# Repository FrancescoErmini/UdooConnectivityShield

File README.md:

# UdooConnectivityShield

Gerber file used to create a shield for UDOO quad board to use XBEE and NFC module by Adafruit.
Video description here: http://www.francescoermini.it/?p=2317

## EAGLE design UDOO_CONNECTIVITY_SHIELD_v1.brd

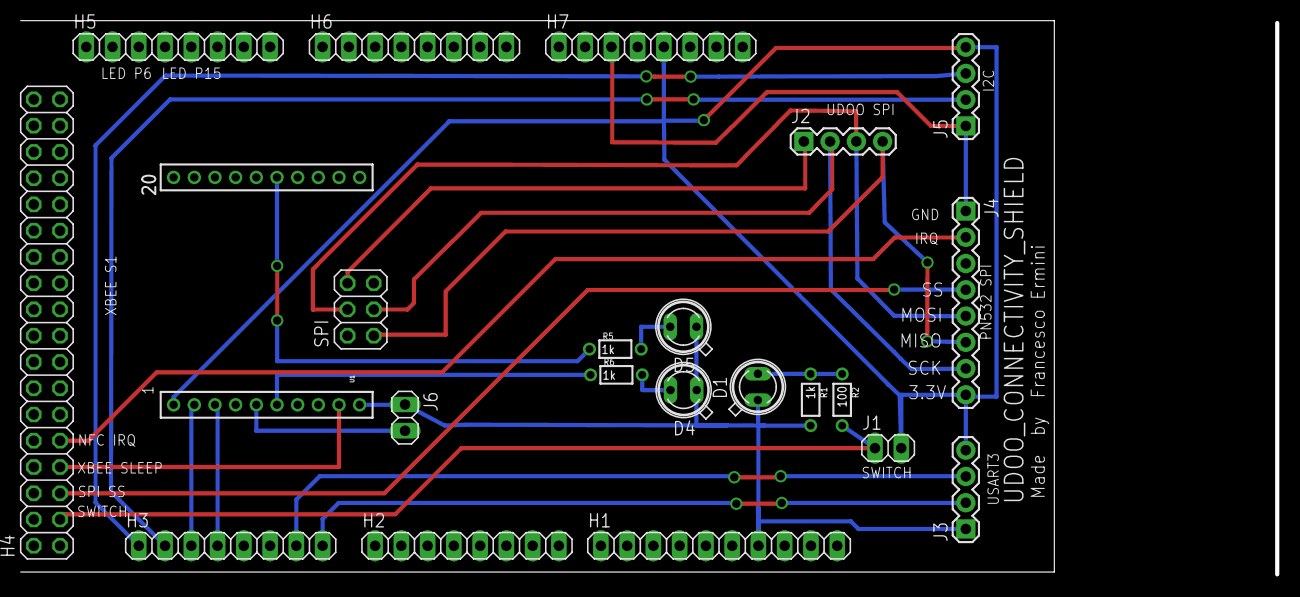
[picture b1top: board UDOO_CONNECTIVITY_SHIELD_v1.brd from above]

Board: 2 copper layers, 121.6 x 53.6 mm, 22 parts (0 on the bottom side), 23 nets.

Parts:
D1, D4, D5: SFH480
H1: 1X10
H2, H3, H5, H6, H7: 1X08
H4: 2X18
J1, J6: 1X02
J2, J3, J5: 1X04
J4: 1X08
R1, R5, R6: 1k; 1/6W-RES
R2: 100; 1/6W-RES
SPI: 2X03
U1: XBEE; XBEE-1

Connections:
S$1: H7.5, J1.2, J3.4, J4.8, J5.4, U1.1
S$3: H3.1, J5.3
S$5: H3.4, U1.3
S$6: H3.3, U1.2
S$7: H4.3, J1.1, R2.2
S$8: J2.4, J4.6, SPI.1
S$9: J2.2, J4.7, SPI.3
S$10: J6.2, U1.5
S$11: J2.1, SPI.6
S$12: J2.3, J4.5, SPI.4
S$13: H4.5, J4.4
S$14: H4.7, U1.9
S$15: H3.7, J3.3
S$16: D1.A, R1.1, R2.1
S$17: R6.1, U1.6
S$18: H4.9, J4.2
S$19: R5.1, U1.15
S$21: H3.2, J5.2
S$22: H7.3, J4.1, J5.1
S$23: H3.8, J3.2
S$24: D1.K, D4.K, D5.K, H1.7, J3.1, J6.1, R1.2, U1.10
S$25: D5.A, R5.2
S$26: D4.A, R6.2

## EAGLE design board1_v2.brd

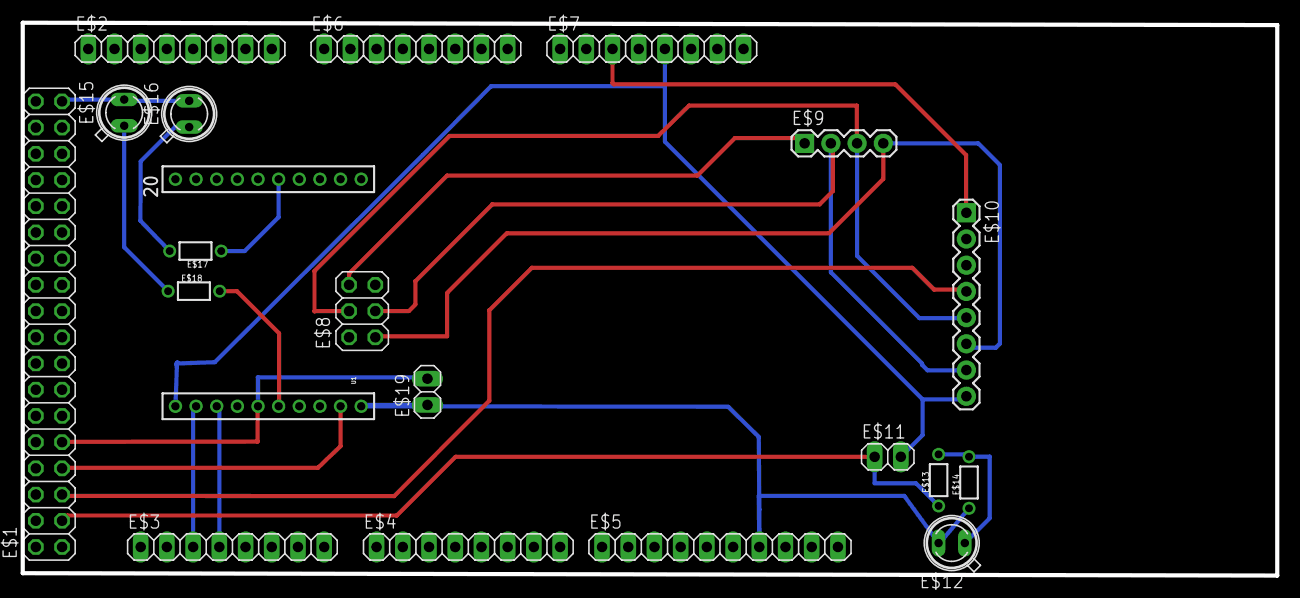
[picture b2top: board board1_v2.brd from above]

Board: 2 copper layers, 121.6 x 53.6 mm, 20 parts (0 on the bottom side), 17 nets.

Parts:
E$1: 2X18
E$2, E$3, E$4, E$6, E$7, E$10: 1X08
E$5: 1X10
E$8: 2X03
E$9: 1X04
E$11, E$19: 1X02
E$12, E$15, E$16: SFH480
E$13, E$14, E$17, E$18: 1/6W-RES
U1: XBEE; XBEE-1

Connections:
S$1: E$7.5, E$10.8, E$11.2, U1.1
S$3: E$7.3, E$10.1
S$5: E$3.4, U1.3
S$6: E$3.3, U1.2
S$7: E$1.3, E$11.1, E$13.1
S$8: E$8.1, E$9.4, E$10.6
S$9: E$8.3, E$9.2, E$10.7
S$10: E$19.2, U1.5
S$11: E$8.6, E$9.1
S$12: E$8.4, E$9.3, E$10.5
S$15: E$5.7, E$12.A, E$14.1, E$19.1, U1.10
S$16: E$12.K, E$13.2, E$14.2
S$18: E$1.35, E$15.A, E$16.A
S$19: E$17.1, U1.15
S$21: E$16.K, E$17.2
S$22: E$15.K, E$18.1
S$23: E$18.2, U1.6

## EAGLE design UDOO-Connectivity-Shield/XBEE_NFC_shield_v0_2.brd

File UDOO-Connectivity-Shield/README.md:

UDOO CONNECTIVITY BOARD

This is a first prototipe of the shield. 
This shield is useful for plug an Xbee Module and an Adafruit NFC shield.

ISSUE: The antenna part of the NFC Shield cover all the GPIO.

@TODO In next revision of this prototipe I am plannig to turn of the NFC module of 180°.
The Antenna Part will be above the Freascale dissipator.
@TODO Insert a switch for turn xbee/nfc on/off
@TODO Insert Led for xbee
@TODO Study of BLE module included in the shield
@TODO Drow connector for a numeric keypad

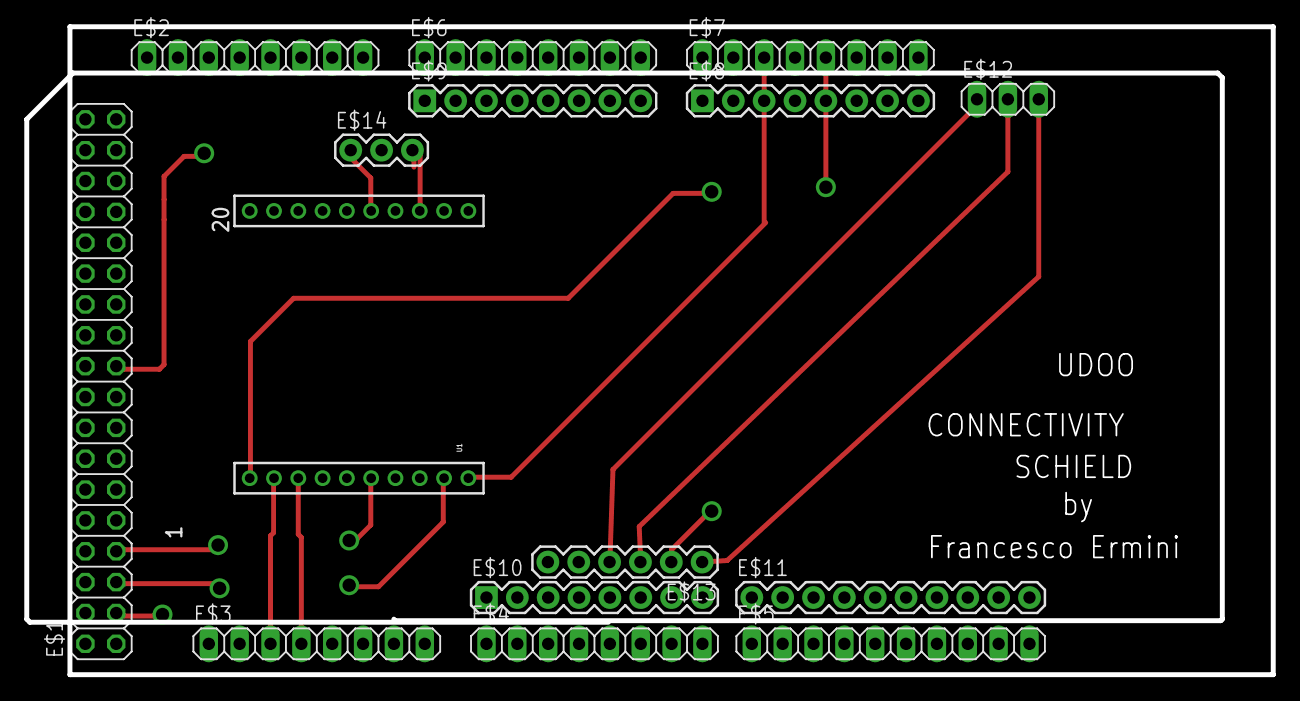
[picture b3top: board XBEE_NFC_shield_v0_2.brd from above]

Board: 2 copper layers, 102.6 x 53.3 mm, 15 parts (0 on the bottom side), 7 nets.

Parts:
E$1: 2X18
E$2, E$3, E$4, E$6, E$7, E$8, E$9, E$10: 1X08
E$5, E$11: 1X10
E$12, E$14: 1X03
E$13: 1X06
U1: XBEE; XBEE-1

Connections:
S$4: E$7.5, E$8.5
S$5: E$7.3, E$8.3
S$6: E$3.3, U1.2
S$7: E$3.4, U1.3
S$8: E$12.1, E$13.4
S$9: E$12.2, E$13.3
S$10: E$12.3, E$13.1

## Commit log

2015-03-29 First version of Udoo Connectivity Shield
2015-03-29 Add Info on the shield
2015-03-29 Add immage preview of Udoo Connectivity Shield
2015-03-29 Add readne, TODO, and Advice
2015-04-07 new PCB prototype
2015-04-09 First release of UDOO CONNECTIVITY SHIELD
2015-04-09 Add link from GPIO_3 (pin 31) to NFC IRQ pin
2015-04-09 Add XBEE and NFC shematic file connections
2015-05-04 Final Revision of the UDOO SHIELD
2015-05-04 Final Revision Gerber files to send the fab house
2015-05-04 Final revision immage of brd shield
2015-07-13 UDOO CONNECTIVITY SHIELD Eagle PCB design and Gerber Files

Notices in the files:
parts and their libraries:
SparkFun-Connectors: Licensing: Creative Commons ShareAlike 4.0 International - https://creativecommons.org/licenses/by-sa/4.0
